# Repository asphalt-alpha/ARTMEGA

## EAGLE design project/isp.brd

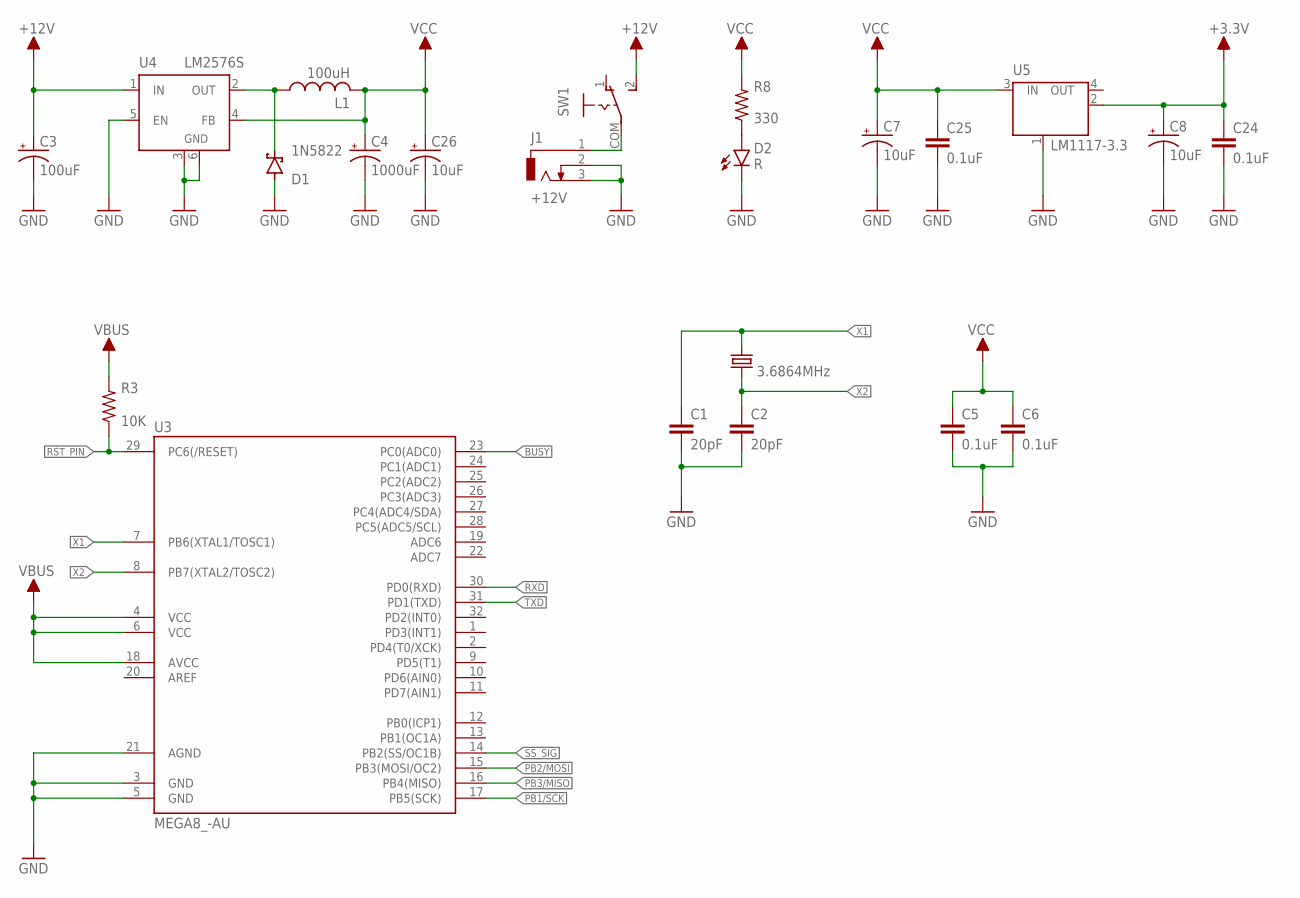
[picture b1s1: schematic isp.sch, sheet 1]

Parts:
C1, C2: 20pF; C0603
C3: 100uF; 153CLV-0807
C4: 1000uF; MVG_K14
C5, C6, C24, C25: 0.1uF; C0603
C7, C8, C26: 10uF; 153CLV-0605
D1: 1N5822; DO201T15
D2: R; LED3MM
J1: +12V; DCJ0303
L1: 100uH; 212-032T2
R3: 10K; R0603
R8: 330; R0603
SW1: SLIDE-SW-DIP; SLIDE-SW-DIP-SHIELD
U3: MEGA8_-AU; TQFP32-08
U4: LM2576S; TO263-5
U5: LM1117-3.3; SOT223
Y1: 3.6864MHz; HC49UP

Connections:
+3.3V: C8.+, C24.1, U5.2 (OUT); also elsewhere on the board
+12V: C3.+, SW1.2, U4.1 (IN); also elsewhere on the board
BUSY: U3.23 (PC0(ADC0)); also elsewhere on the board
GND: C1.2, C2.2, C3.-, C4.-, C5.2, C6.2, C7.-, C8.-, C24.2, C25.2, C26.-, D1.A, D2.K (C), J1.2, J1.3, U3.3 (GND), U3.5 (GND), U3.21 (AGND), U4.3 (GND), U4.5 (EN), U4.6 (GND), U5.1 (GND/ADJ); also elsewhere on the board
unnamed: D1.C, L1.1, U4.2 (OUT)
unnamed: D2.A, R8.1
PB1/SCK: U3.17 (PB5(SCK)); also elsewhere on the board
PB2/MOSI: U3.15 (PB3(MOSI/OC2)); also elsewhere on the board
PB3/MISO: U3.16 (PB4(MISO)); also elsewhere on the board
RST_PIN: R3.1, U3.29 (PC6(/RESET)); also elsewhere on the board
RXD: U3.30 (PD0(RXD)); also elsewhere on the board
SS_SIG: U3.14 (PB2(SS/OC1B)); also elsewhere on the board
TXD: U3.31 (PD1(TXD)); also elsewhere on the board
VBUS: R3.2, U3.4 (VCC), U3.6 (VCC), U3.18 (AVCC); also elsewhere on the board
VCC: C4.+, C5.1, C6.1, C7.+, C25.1, C26.+, L1.2, R8.2, U4.4 (FB), U5.3 (IN); also elsewhere on the board
X1: C1.1, U3.7 (PB6(XTAL1/TOSC1)), Y1.2
X2: C2.1, U3.8 (PB7(XTAL2/TOSC2)), Y1.1

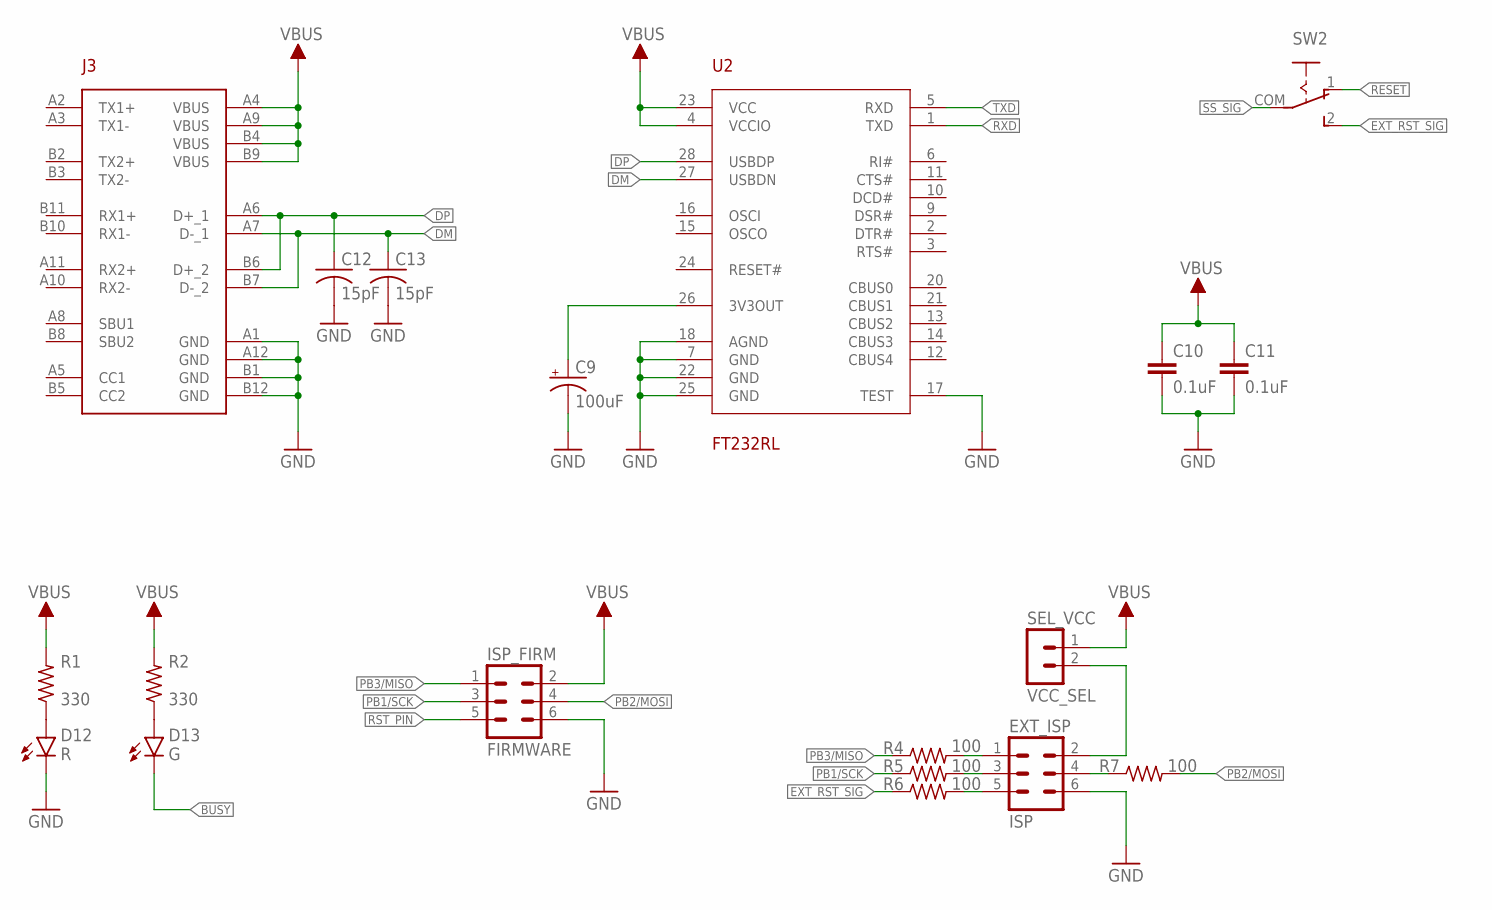
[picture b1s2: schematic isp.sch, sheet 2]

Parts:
C9: 100uF; 153CLV-0807
C10, C11: 0.1uF; C0603
C12, C13: 15pF; C0603
D12: R; LED3MM
D13: G; LED3MM
EXT_ISP: ISP; ML6
ISP_FIRM: FIRMWARE; MA03-2
J3: USB-C-SMD; USB3.1-C-SMD
R1, R2: 330; R0603
R4, R5, R6, R7: 100; R0603
SEL_VCC: VCC_SEL; MA02-1
SW2: SLIDE-SW-DIP; SLIDE-SW-DIP-SHIELD
U2: FT232RL; SSOP28

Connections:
BUSY: D13.K (C); also elsewhere on the board
DM: C13.1, J3.A7 (D-_1), J3.B7 (D-_2), U2.27 (USBDN)
DP: C12.1, J3.A6 (D+_1), J3.B6 (D+_2), U2.28 (USBDP)
EXT_RST_SIG: R6.1, SW2.2
GND: C9.-, C10.2, C11.2, C12.2, C13.2, D12.K (C), EXT_ISP.6, ISP_FIRM.6, J3.A1 (GND), J3.A12 (GND), J3.B1 (GND), J3.B12 (GND), U2.7 (GND), U2.17 (TEST), U2.18 (AGND), U2.22 (GND), U2.25 (GND); also elsewhere on the board
unnamed: D12.A, R1.1
unnamed: D13.A, R2.1
unnamed: EXT_ISP.1, R4.2
unnamed: EXT_ISP.3, R5.2
unnamed: EXT_ISP.5, R6.2
unnamed: EXT_ISP.4, R7.1
unnamed: EXT_ISP.2, SEL_VCC.2
unnamed: C9.+, U2.26 (3V3OUT)
PB1/SCK: ISP_FIRM.3, R5.1; also elsewhere on the board
PB2/MOSI: ISP_FIRM.4, R7.2; also elsewhere on the board
PB3/MISO: ISP_FIRM.1, R4.1; also elsewhere on the board
RESET: SW2.1; also elsewhere on the board
RST_PIN: ISP_FIRM.5; also elsewhere on the board
RXD: U2.1 (TXD); also elsewhere on the board
SS_SIG: SW2.COM; also elsewhere on the board
TXD: U2.5 (RXD); also elsewhere on the board
VBUS: C10.1, C11.1, ISP_FIRM.2, J3.A4 (VBUS), J3.A9 (VBUS), J3.B4 (VBUS), J3.B9 (VBUS), R1.2, R2.2, SEL_VCC.1, U2.4 (VCCIO), U2.23 (VCC); also elsewhere on the board

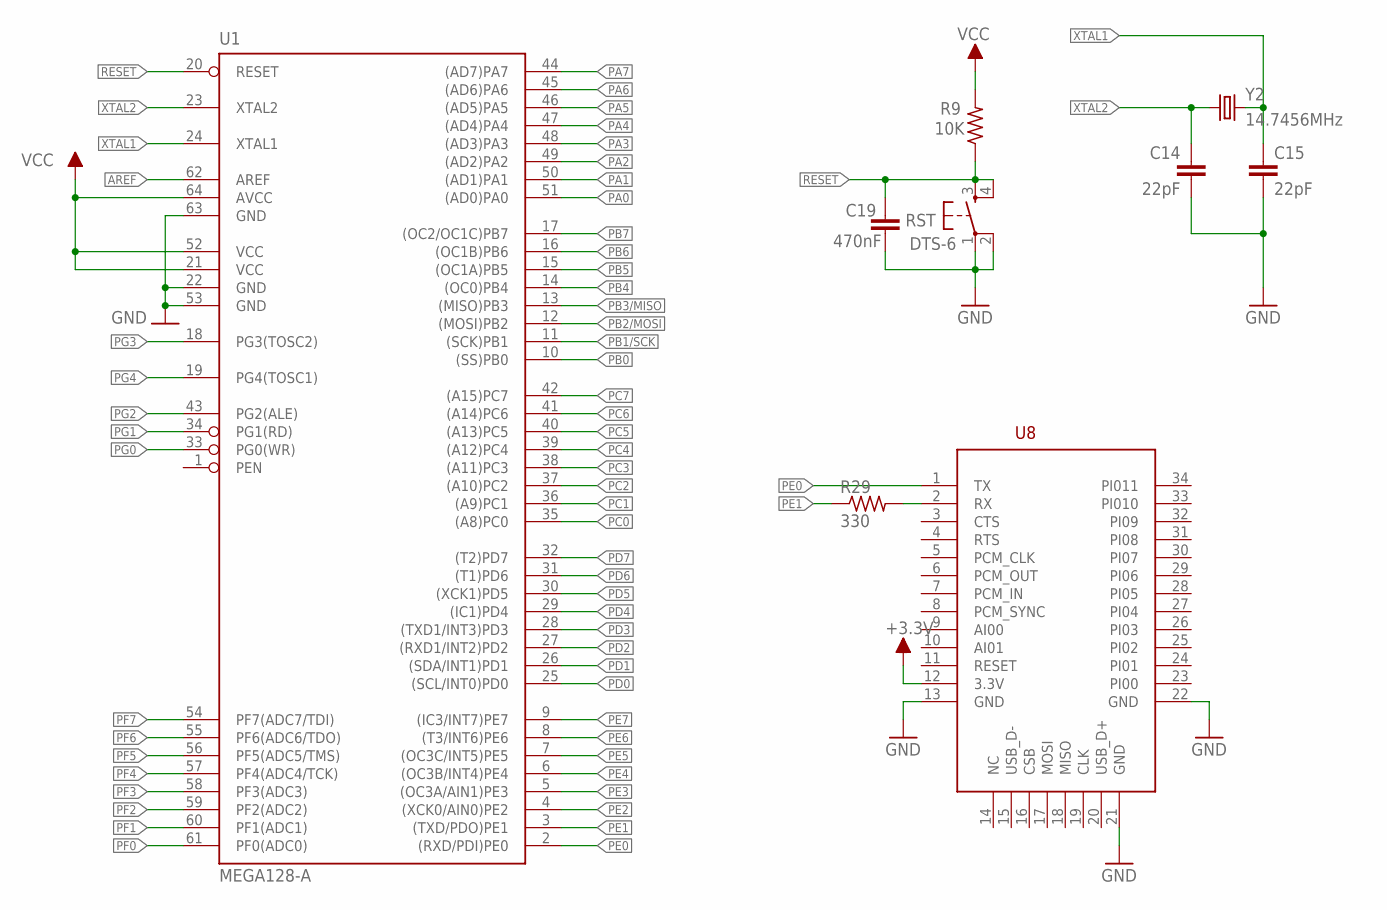
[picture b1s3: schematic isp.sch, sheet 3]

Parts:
C14, C15: 22pF; C0603
C19: 470nF; C1206
R9: 10K; R0603
R29: 330; R0603
RST: DTS-6
U1: MEGA128-A; TQFP64
U8: HC06-SMD
Y2: 14.7456MHz; HC49UP

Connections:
+3.3V: U8.12 (3.3V); also elsewhere on the board
AREF: U1.62 (AREF); also elsewhere on the board
GND: C14.1, C15.2, C19.2, RST.1, RST.2, U1.22 (GND), U1.53 (GND), U1.63 (GND), U8.13 (GND), U8.21 (GND), U8.22 (GND); also elsewhere on the board
unnamed: R29.2, U8.2 (RX)
PA0: U1.51 ((AD0)PA0); also elsewhere on the board
PA1: U1.50 ((AD1)PA1); also elsewhere on the board
PA2: U1.49 ((AD2)PA2); also elsewhere on the board
PA3: U1.48 ((AD3)PA3); also elsewhere on the board
PA4: U1.47 ((AD4)PA4); also elsewhere on the board
PA5: U1.46 ((AD5)PA5); also elsewhere on the board
PA6: U1.45 ((AD6)PA6); also elsewhere on the board
PA7: U1.44 ((AD7)PA7); also elsewhere on the board
PB0: U1.10 ((SS)PB0); also elsewhere on the board
PB1/SCK: U1.11 ((SCK)PB1); also elsewhere on the board
PB2/MOSI: U1.12 ((MOSI)PB2); also elsewhere on the board
PB3/MISO: U1.13 ((MISO)PB3); also elsewhere on the board
PB4: U1.14 ((OC0)PB4); also elsewhere on the board
PB5: U1.15 ((OC1A)PB5); also elsewhere on the board
PB6: U1.16 ((OC1B)PB6); also elsewhere on the board
PB7: U1.17 ((OC2/OC1C)PB7); also elsewhere on the board
PC0: U1.35 ((A8)PC0); also elsewhere on the board
PC1: U1.36 ((A9)PC1); also elsewhere on the board
PC2: U1.37 ((A10)PC2); also elsewhere on the board
PC3: U1.38 ((A11)PC3); also elsewhere on the board
PC4: U1.39 ((A12)PC4); also elsewhere on the board
PC5: U1.40 ((A13)PC5); also elsewhere on the board
PC6: U1.41 ((A14)PC6); also elsewhere on the board
PC7: U1.42 ((A15)PC7); also elsewhere on the board
PD0: U1.25 ((SCL/INT0)PD0); also elsewhere on the board
PD1: U1.26 ((SDA/INT1)PD1); also elsewhere on the board
PD2: U1.27 ((RXD1/INT2)PD2); also elsewhere on the board
PD3: U1.28 ((TXD1/INT3)PD3); also elsewhere on the board
PD4: U1.29 ((IC1)PD4); also elsewhere on the board
PD5: U1.30 ((XCK1)PD5); also elsewhere on the board
PD6: U1.31 ((T1)PD6); also elsewhere on the board
PD7: U1.32 ((T2)PD7); also elsewhere on the board
PE0: U1.2 ((RXD/PDI)PE0), U8.1 (TX)
PE1: R29.1, U1.3 ((TXD/PDO)PE1)
PE2: U1.4 ((XCK0/AIN0)PE2); also elsewhere on the board
PE3: U1.5 ((OC3A/AIN1)PE3); also elsewhere on the board
PE4: U1.6 ((OC3B/INT4)PE4); also elsewhere on the board
PE5: U1.7 ((OC3C/INT5)PE5); also elsewhere on the board
PE6: U1.8 ((T3/INT6)PE6); also elsewhere on the board
PE7: U1.9 ((IC3/INT7)PE7); also elsewhere on the board
PF0: U1.61 (PF0(ADC0)); also elsewhere on the board
PF1: U1.60 (PF1(ADC1)); also elsewhere on the board
PF2: U1.59 (PF2(ADC2)); also elsewhere on the board
PF3: U1.58 (PF3(ADC3)); also elsewhere on the board
PF4: U1.57 (PF4(ADC4/TCK)); also elsewhere on the board
PF5: U1.56 (PF5(ADC5/TMS)); also elsewhere on the board
PF6: U1.55 (PF6(ADC6/TDO)); also elsewhere on the board
PF7: U1.54 (PF7(ADC7/TDI)); also elsewhere on the board
PG0: U1.33 (PG0(WR)); also elsewhere on the board
PG1: U1.34 (PG1(RD)); also elsewhere on the board
PG2: U1.43 (PG2(ALE)); also elsewhere on the board
PG3: U1.18 (PG3(TOSC2)); also elsewhere on the board
PG4: U1.19 (PG4(TOSC1)); also elsewhere on the board
RESET: C19.1, R9.1, RST.3, RST.4, U1.20 (RESET); also elsewhere on the board
VCC: R9.2, U1.21 (VCC), U1.52 (VCC), U1.64 (AVCC); also elsewhere on the board
XTAL1: C15.1, U1.24 (XTAL1), Y2.1
XTAL2: C14.2, U1.23 (XTAL2), Y2.2

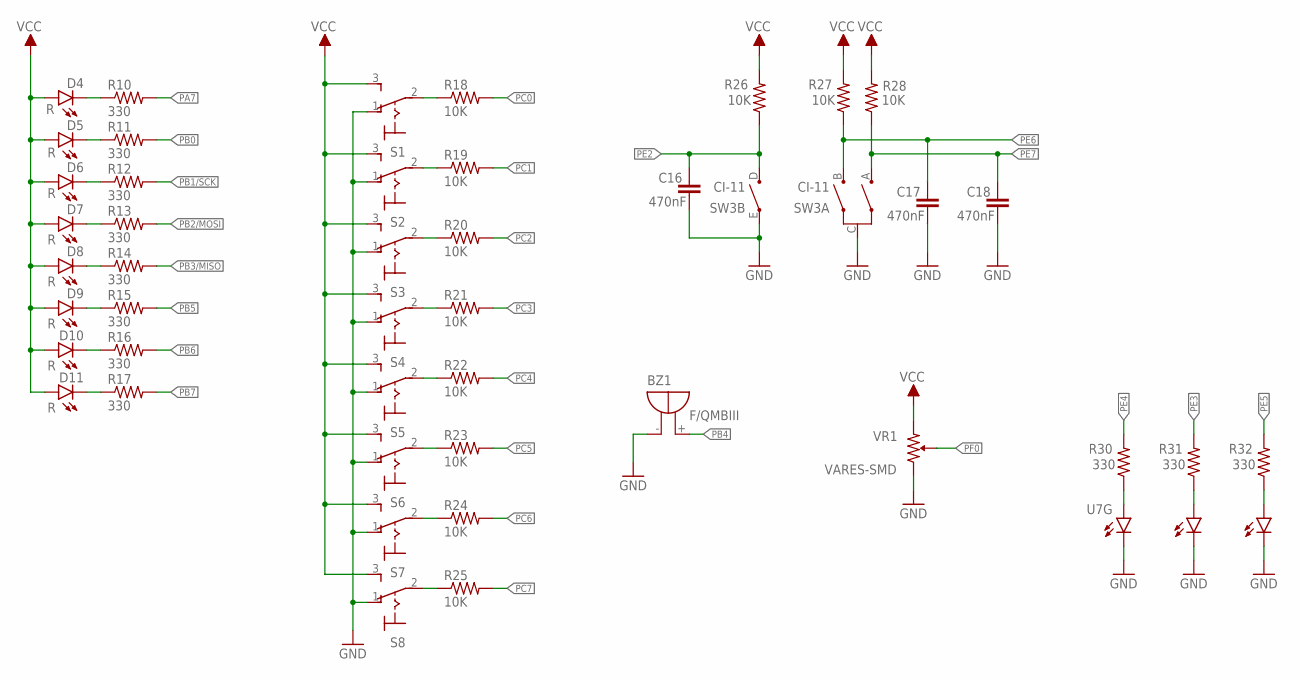
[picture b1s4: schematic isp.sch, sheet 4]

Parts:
BZ1: F/QMBIII
C16, C17, C18: 470nF; C1206
D4, D5, D6, D7, D8, D9, D10, D11: R; LED3MM
R10, R11, R12, R13, R14, R15, R16, R17, R30, R31, R32: 330; R0603
R18, R19, R20, R21, R22, R23, R24, R25, R26, R27, R28: 10K; R0603
S1, S2, S3, S4, S5, S6, S7, S8: M9040P
SW3: CI-11
U7: LP2C63-ST-RGB-SR0
VR1: VARES-SMD

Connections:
GND: BZ1.- (+), C16.2, C17.2, C18.2, S1.1 (O), S2.1 (O), S3.1 (O), S4.1 (O), S5.1 (O), S6.1 (O), S7.1 (O), S8.1 (O), SW3.C, SW3.E, U7.4 (C), U7.5 (C), U7.6 (C), VR1.1; also elsewhere on the board
unnamed: D4.K (C), R10.1
unnamed: D5.K (C), R11.1
unnamed: D6.K (C), R12.1
unnamed: D7.K (C), R13.1
unnamed: D8.K (C), R14.1
unnamed: D9.K (C), R15.1
unnamed: D10.K (C), R16.1
unnamed: D11.K (C), R17.1
unnamed: R18.1, S1.2
unnamed: R19.1, S2.2
unnamed: R20.1, S3.2
unnamed: R21.1, S4.2
unnamed: R22.1, S5.2
unnamed: R23.1, S6.2
unnamed: R24.1, S7.2
unnamed: R25.1, S8.2
unnamed: R30.1, U7.1 (A)
unnamed: R31.1, U7.2 (A)
unnamed: R32.1, U7.3 (A)
PA7: R10.2; also elsewhere on the board
PB0: R11.2; also elsewhere on the board
PB1/SCK: R12.2; also elsewhere on the board
PB2/MOSI: R13.2; also elsewhere on the board
PB3/MISO: R14.2; also elsewhere on the board
PB4: BZ1.+ (-); also elsewhere on the board
PB5: R15.2; also elsewhere on the board
PB6: R16.2; also elsewhere on the board
PB7: R17.2; also elsewhere on the board
PC0: R18.2; also elsewhere on the board
PC1: R19.2; also elsewhere on the board
PC2: R20.2; also elsewhere on the board
PC3: R21.2; also elsewhere on the board
PC4: R22.2; also elsewhere on the board
PC5: R23.2; also elsewhere on the board
PC6: R24.2; also elsewhere on the board
PC7: R25.2; also elsewhere on the board
PE2: C16.1, R26.1, SW3.D; also elsewhere on the board
PE3: R31.2; also elsewhere on the board
PE4: R30.2; also elsewhere on the board
PE5: R32.2; also elsewhere on the board
PE6: C17.1, R27.1, SW3.B; also elsewhere on the board
PE7: C18.1, R28.1, SW3.A; also elsewhere on the board
PF0: VR1.2; also elsewhere on the board
VCC: D4.A, D5.A, D6.A, D7.A, D8.A, D9.A, D10.A, D11.A, R26.2, R27.2, R28.2, S1.3 (S), S2.3 (S), S3.3 (S), S4.3 (S), S5.3 (S), S6.3 (S), S7.3 (S), S8.3 (S), VR1.3; also elsewhere on the board

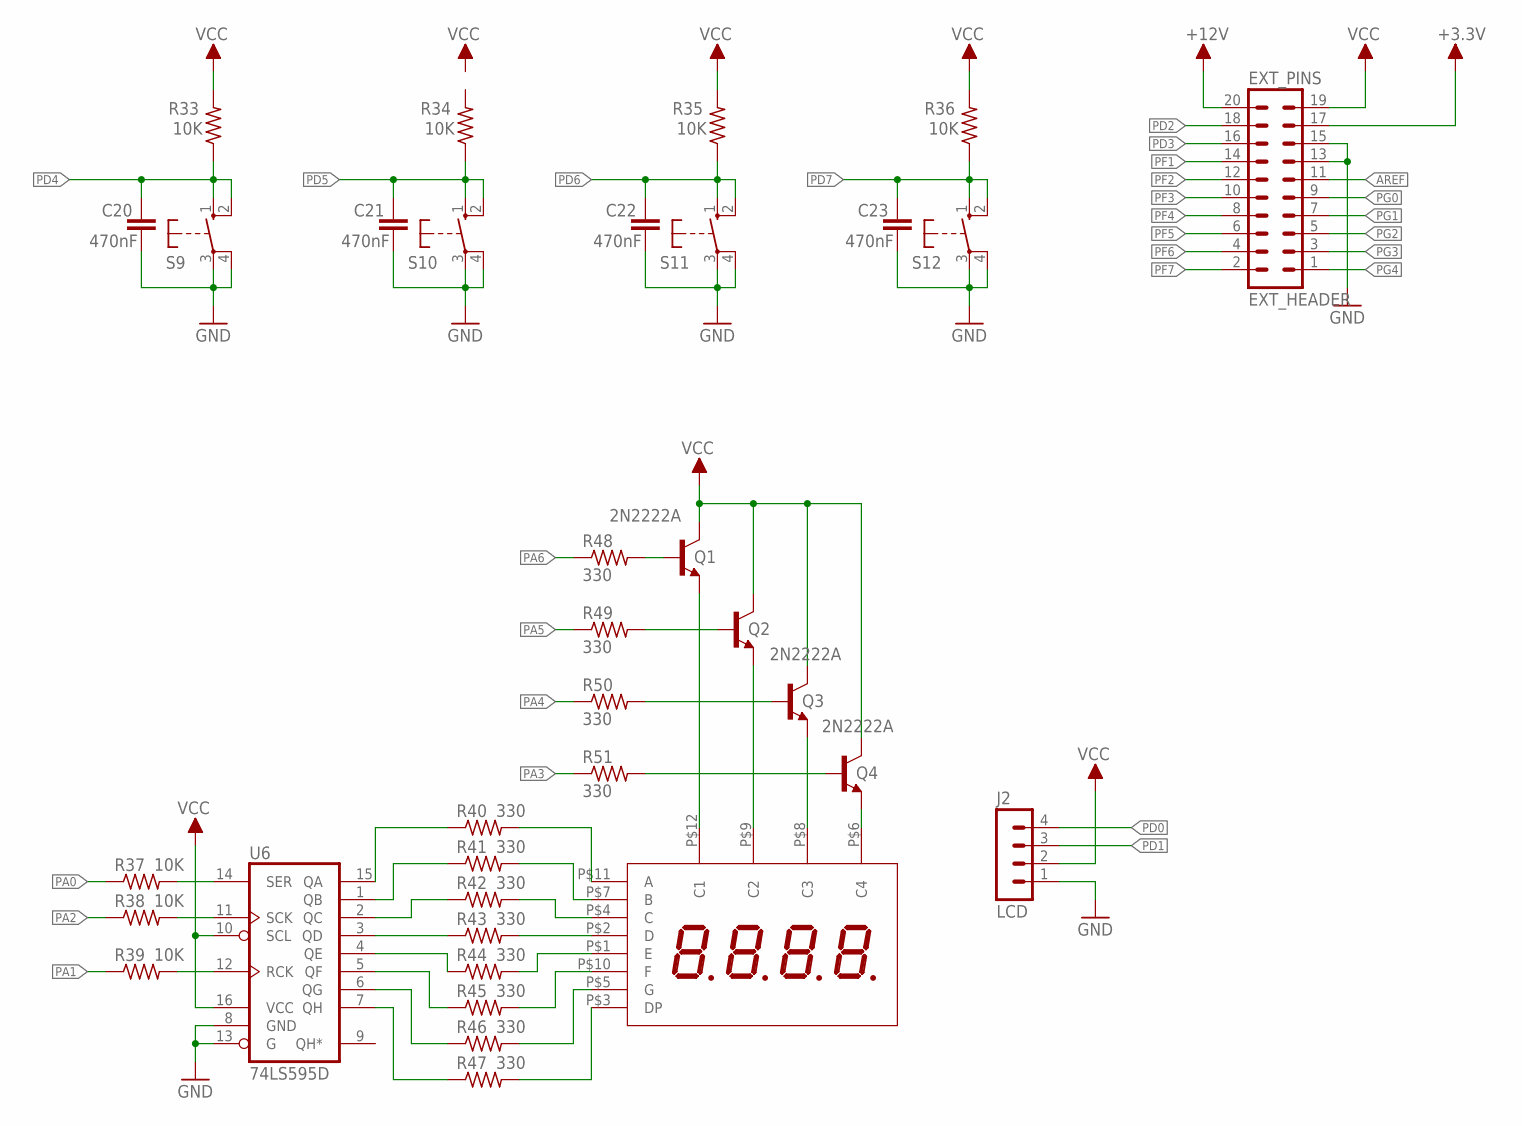
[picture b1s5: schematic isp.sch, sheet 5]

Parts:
C20, C21, C22, C23: 470nF; C1206
D3: 4CH_FND-DIP
EXT_PINS: EXT_HEADER; MA10-2
J2: LCD; MA04-1
Q1, Q2, Q3, Q4: 2N2222A; TO92-EBC
R33, R34, R35, R36, R37, R38, R39: 10K; R0603
R40, R41, R42, R43, R44, R45, R46, R47, R48, R49, R50, R51: 330; R0603
S9, S10, S11, S12: RACON12
U6: 74LS595D; SO16

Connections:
+3.3V: EXT_PINS.17; also elsewhere on the board
+12V: EXT_PINS.20; also elsewhere on the board
AREF: EXT_PINS.11; also elsewhere on the board
GND: C20.2, C21.2, C22.2, C23.2, EXT_PINS.13, EXT_PINS.15, J2.1, S9.3, S9.4, S10.3, S10.4, S11.3, S11.4, S12.3, S12.4, U6.8 (GND), U6.13 (G); also elsewhere on the board
unnamed: R37.2, U6.14 (SER)
unnamed: R39.2, U6.12 (RCK)
unnamed: Q1.B, R48.2
unnamed: Q2.B, R49.2
unnamed: Q3.B, R50.2
unnamed: Q4.B, R51.2
unnamed: D3.P$12 (C1), Q1.E
unnamed: D3.P$9 (C2), Q2.E
unnamed: R38.2, U6.11 (SCK)
unnamed: R40.1, U6.15 (QA)
unnamed: R41.1, U6.1 (QB)
unnamed: R42.1, U6.2 (QC)
unnamed: R43.1, U6.3 (QD)
unnamed: R44.1, U6.4 (QE)
unnamed: R45.1, U6.5 (QF)
unnamed: R46.1, U6.6 (QG)
unnamed: R47.1, U6.7 (QH)
unnamed: D3.P$11 (A), R40.2
unnamed: D3.P$7 (B), R41.2
unnamed: D3.P$4 (C), R42.2
unnamed: D3.P$2 (D), R43.2
unnamed: D3.P$1 (E), R44.2
unnamed: D3.P$10 (F), R45.2
unnamed: D3.P$5 (G), R46.2
unnamed: D3.P$3 (DP), R47.2
unnamed: D3.P$8 (C3), Q3.E
unnamed: D3.P$6 (C4), Q4.E
PA0: R37.1; also elsewhere on the board
PA1: R39.1; also elsewhere on the board
PA2: R38.1; also elsewhere on the board
PA3: R51.1; also elsewhere on the board
PA4: R50.1; also elsewhere on the board
PA5: R49.1; also elsewhere on the board
PA6: R48.1; also elsewhere on the board
PD0: J2.4; also elsewhere on the board
PD1: J2.3; also elsewhere on the board
PD2: EXT_PINS.18; also elsewhere on the board
PD3: EXT_PINS.16; also elsewhere on the board
PD4: C20.1, R33.1, S9.1 (S), S9.2 (S); also elsewhere on the board
PD5: C21.1, R34.1, S10.1 (S), S10.2 (S); also elsewhere on the board
PD6: C22.1, R35.1, S11.1 (S), S11.2 (S); also elsewhere on the board
PD7: C23.1, R36.1, S12.1 (S), S12.2 (S); also elsewhere on the board
PF1: EXT_PINS.14; also elsewhere on the board
PF2: EXT_PINS.12; also elsewhere on the board
PF3: EXT_PINS.10; also elsewhere on the board
PF4: EXT_PINS.8; also elsewhere on the board
PF5: EXT_PINS.6; also elsewhere on the board
PF6: EXT_PINS.4; also elsewhere on the board
PF7: EXT_PINS.2; also elsewhere on the board
PG0: EXT_PINS.9; also elsewhere on the board
PG1: EXT_PINS.7; also elsewhere on the board
PG2: EXT_PINS.5; also elsewhere on the board
PG3: EXT_PINS.3; also elsewhere on the board
PG4: EXT_PINS.1; also elsewhere on the board
VCC: EXT_PINS.19, J2.2, Q1.C, Q2.C, Q3.C, Q4.C, R33.2, R35.2, R36.2, U6.10 (SCL), U6.16 (VCC); also elsewhere on the board

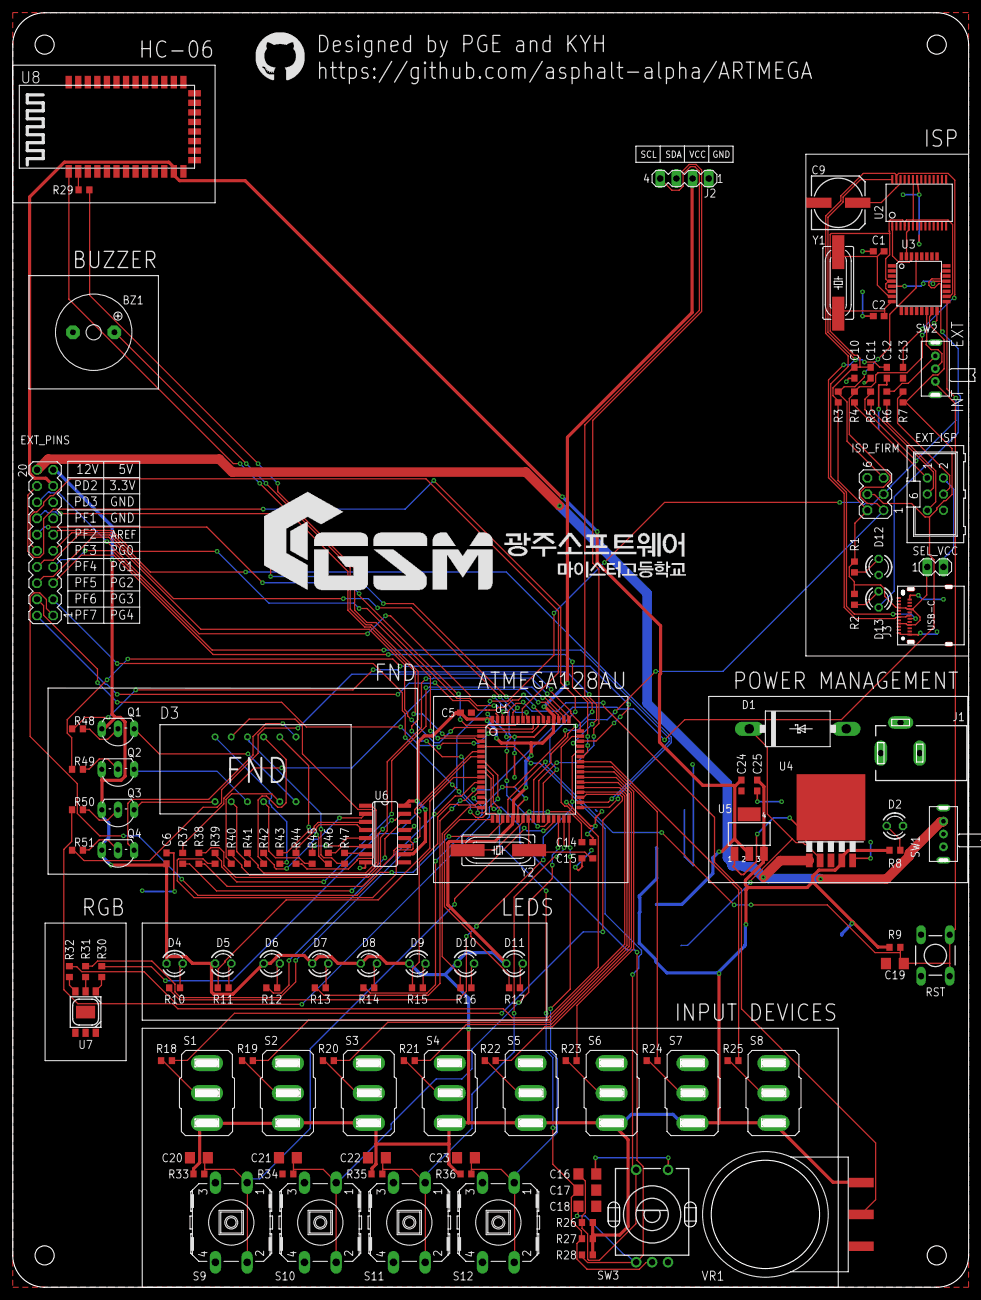
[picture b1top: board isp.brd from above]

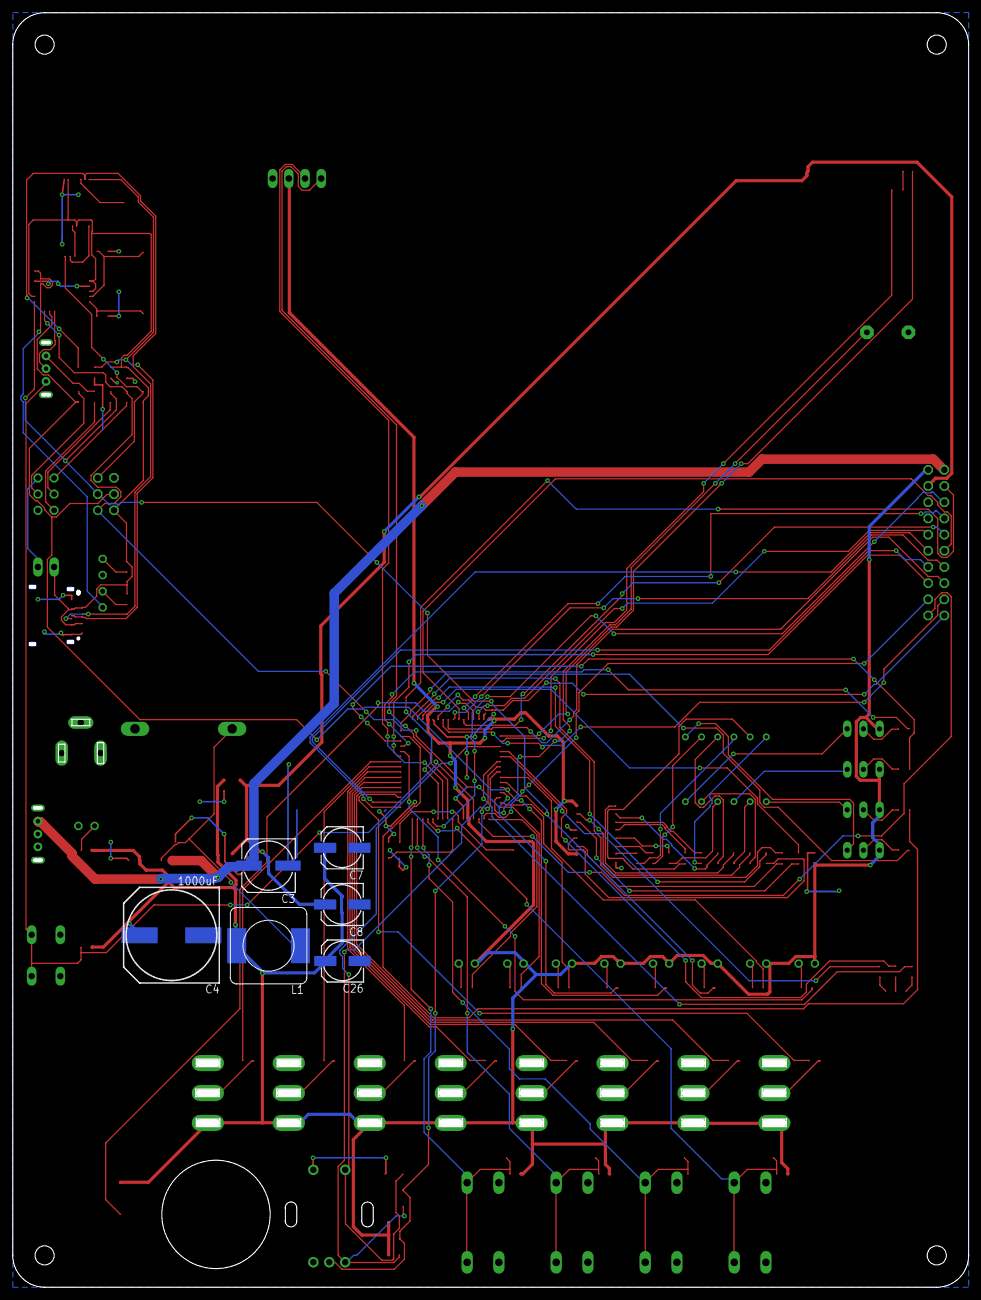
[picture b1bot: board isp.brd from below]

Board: 2 copper layers, 148.8 x 198.8 mm, 130 parts (6 on the bottom side), 129 nets.

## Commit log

2020-09-24 [Added] Version 1
    제작 완료한 스케치와 레이아웃
2020-09-24 [Added] Version 1 libraies
2020-09-24 [Added] Vesion 1 resources
2020-09-24 [Added] Version 1 resources
2020-10-21 [Added] schematic file
2020-10-21 [Changed] file name
2020-10-21 [Added] sample image
